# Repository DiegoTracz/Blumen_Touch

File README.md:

# Interruptor inteligente customizável
O projeto Blumen Touch, é uma solução IoT baseada no ESP8266 com o objetivo de popularizar sistemas de automação residencial de baixo custo.
<h2><b>Introdução</b></h2>
Blumen Touch é um interruptor wi-fi baseado no ESP8266 suportando até 3 botões e 3 relés de estado sólido que suportam 2A cada, 
permitindo controlar até 3 circuitos de iluminação independentes. O Blumen touch foi desenvolvido para ser instalado em caixinhas
4x2, padrão brasileiro, substituindo assim o interruptor padrão que esteja instalado. O controle pode ser feito via comando de voz, via web, smartphone ou manualmente pelos botões.
Além disso possui um interface customizável, onde é possivel colocar qualquer imagem ou foto e customizar como quiser.
<h2><b>Diagrama de fiação </b></h2>
<u1>
  <li> Ligação dos fio para os modelos B1, B2 e B3 </li>
  
  <li> Tutorial instalação:  https://youtu.be/j6668FpMcGA </li>
  <u1>
   <h2>

<h2><b>Bibliotecas necessárias</b></h2>

|  <b>Nome</b> |  <b>Link</b> |
|---|---|
| ArduinoJson  |<a href="https://github.com/bblanchon/ArduinoJson/">GIT</a>  |     
|  WebSockets | <a href="https://github.com/Links2004/arduinoWebSockets/">GIT</a>  |  
| Sirincpro  |  <a href="https://github.com/sinricpro/esp8266-esp32-sdk/">GIT</a> |   
| WifiManager  |<a href="https://github.com/tzapu/WiFiManager/">GIT</a> |   

<h2><b>Hardware</b></h2>
<u1>
  <li> Blumen Touch Placa 1, 2 e 3 teclas frente e trás</li>

  <u1>
   <h2><b>Suporte para placa</b></h2
     
 <u1>
  <li> Suporte (PLA) e espelho (acrilico) </li>

 <u1>
   <h2><b>Esquemáticos</b></h2>
     
<u1>
  <li> Esquematico frente </li>
  
  <li> Esquematico trás </li>

  <u1>
   
  <h2><b>GPIO's</b></h2>

|  <b>GPIO</b> |  <b>PINO</b> |
|---|---|
|16  | BOTÃO 1  |     
|  14 | BOTÃO 2  |  
| 12  |  BOTÃO 3|
| 05  |  RELÉ 1|   
| 04  |  RELÉ 2|   
| 02  |  RELÉ 3|   

  <h2><b>Software necessário</b></h2>
 <li><b>Sirinc Pro</b>: O Sirinc Pro é um serviço de nuvem para dispositivos inteligentes, onde de forma gratuita podemos hospedar até 3 dispositivos gratuitamente e a partir dele fazer o acionamento dos interruptores pelo aplicativo ou comando de voz.</li>
  <li> <b> Passo a passo configuração da placa utilizando a plataforma do Sinric Pro<b>: https://youtu.be/px-q5iuD3NI</li>

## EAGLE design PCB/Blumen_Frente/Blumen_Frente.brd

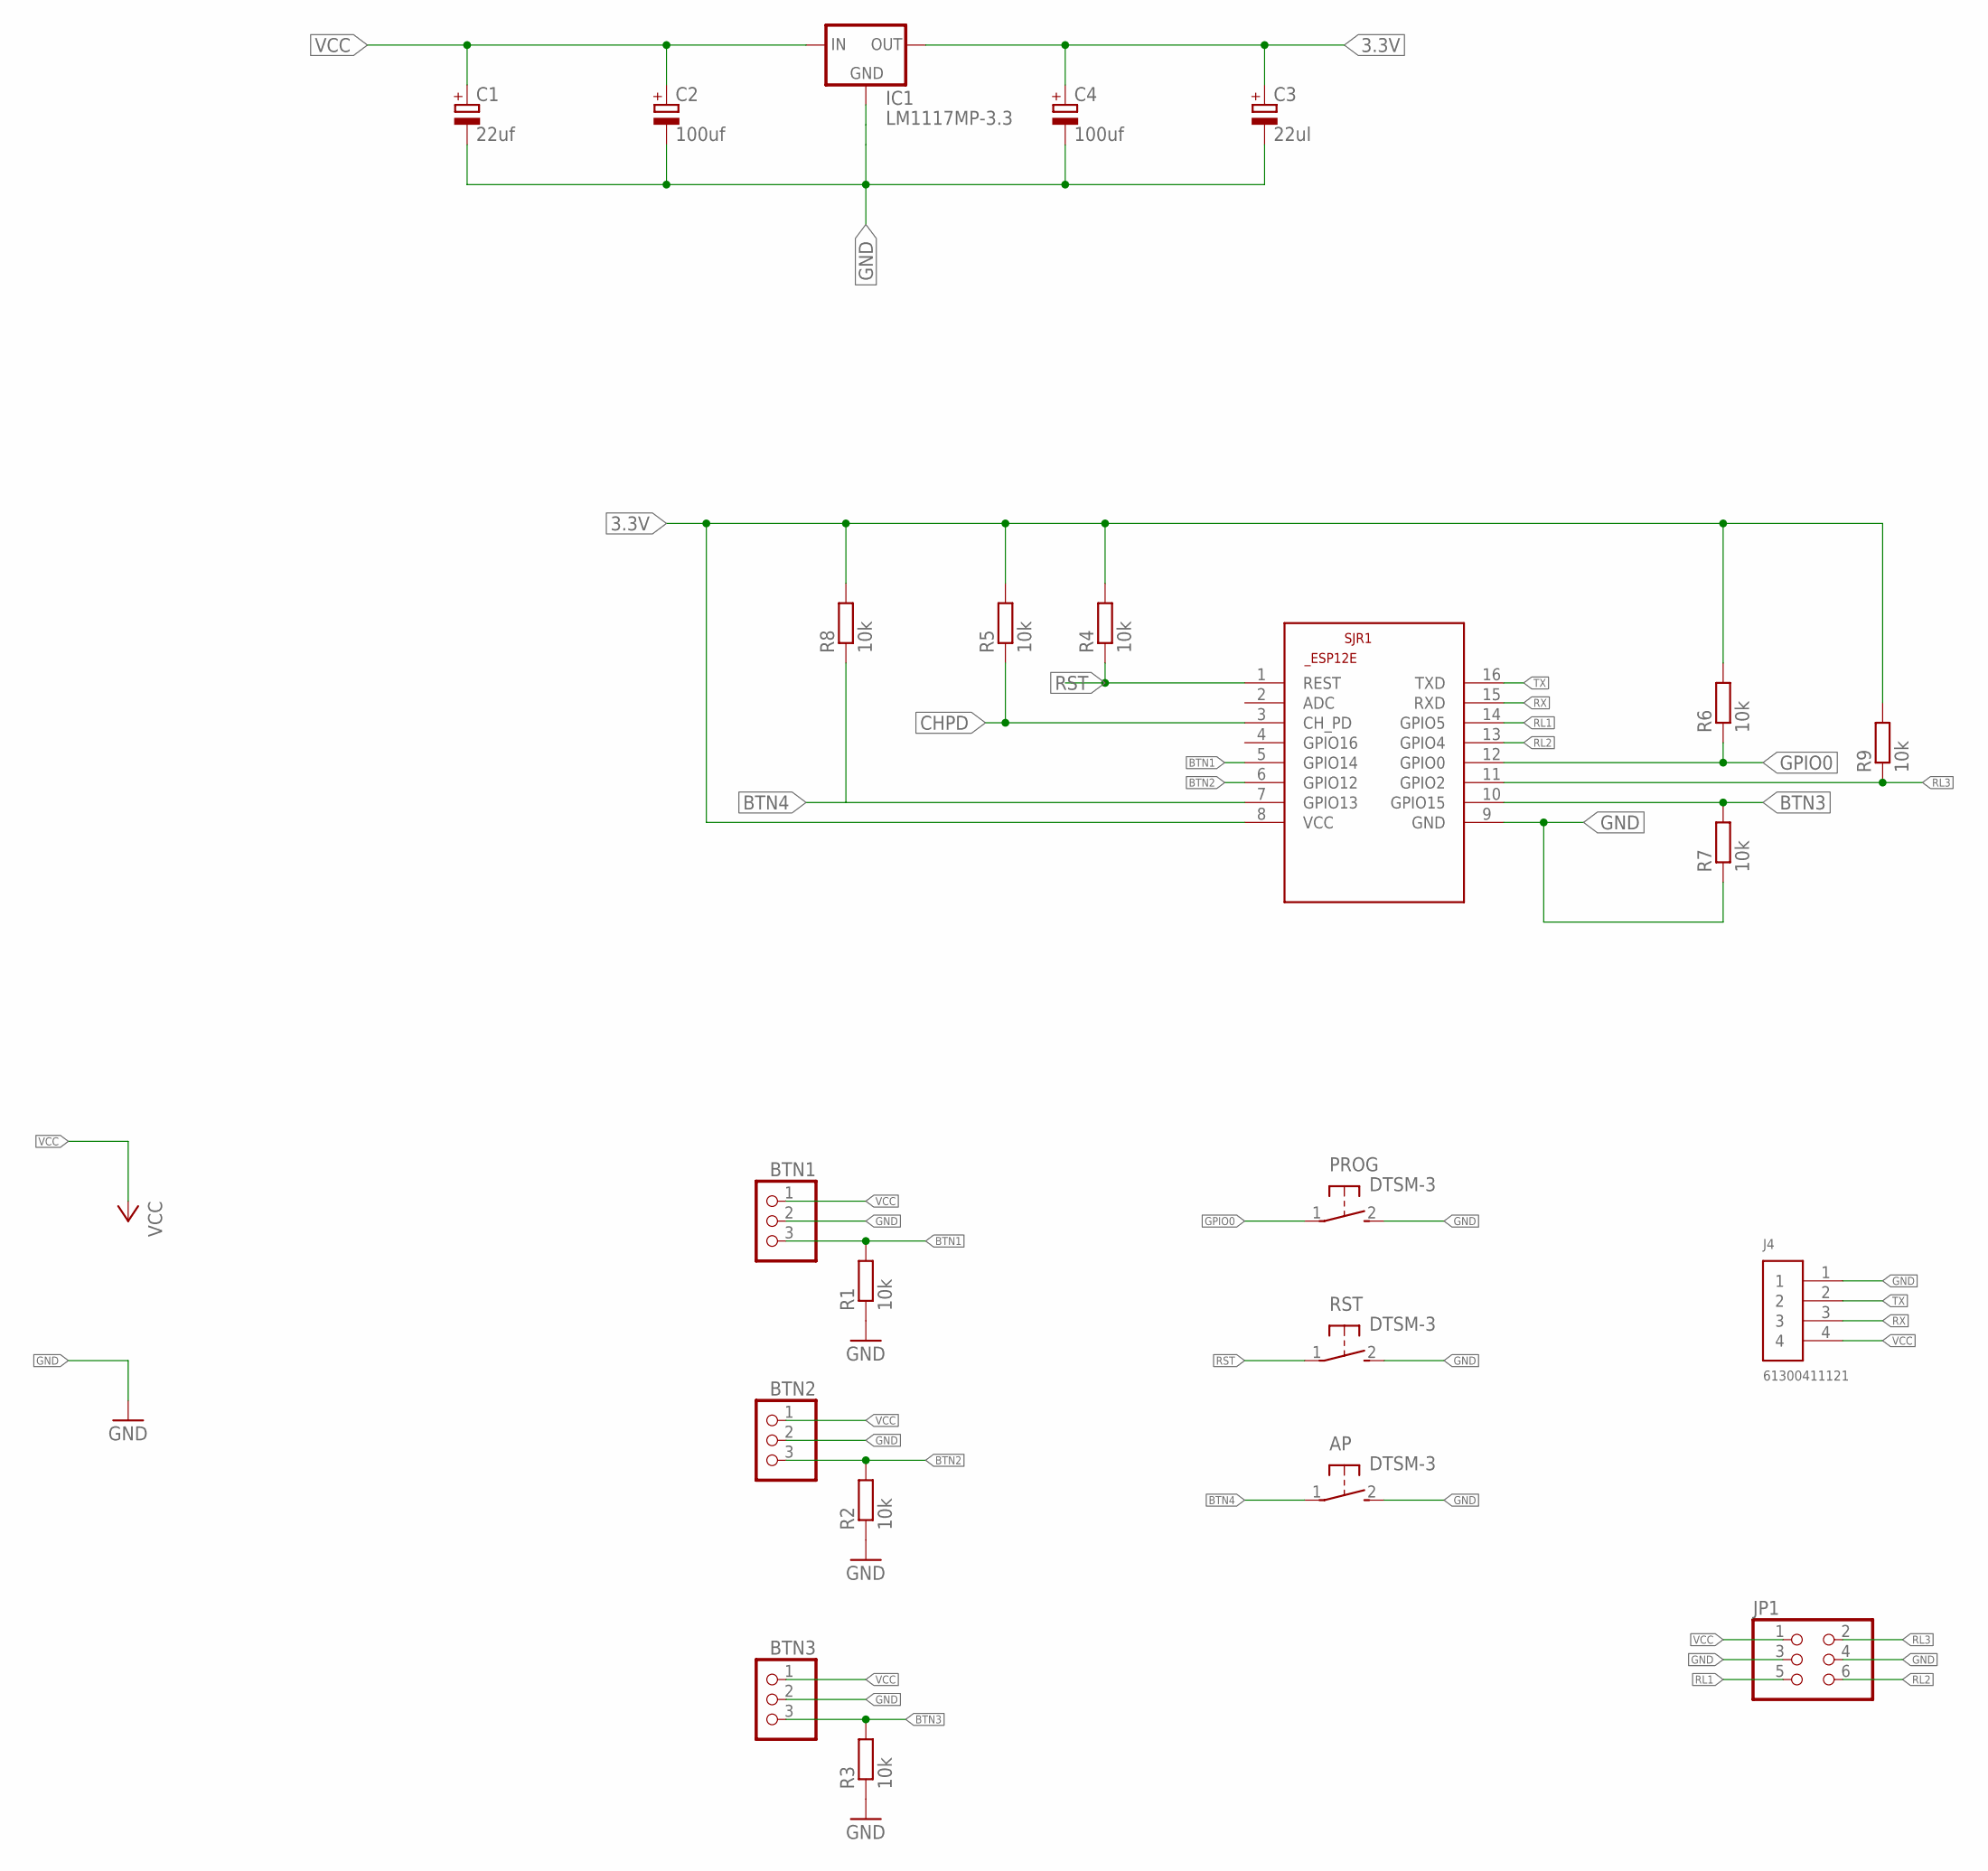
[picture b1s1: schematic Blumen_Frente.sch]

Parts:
AP: DTSM-3
BTN1, BTN2, BTN3: PINHD-1X3; 1X03
C1: 22uf; 153CLV-0505
C2, C4: 100uf; 153CLV-0605
C3: 22ul; 153CLV-0505
IC1: LM1117MP-3.3; SOT223
J4: 61300411121
JP1: PINHD-2X3; 2X03
PROG: DTSM-3
R1, R2, R3, R4, R5, R6, R7, R8, R9: 10k; R0805
RST: DTSM-3
SJR1: ESP8266-12EESP12E; ESP8266-ESP12E

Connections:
3.3V: C3.+, C4.+, IC1.2 (OUT), IC1.4 (OUT), R4.2, R5.2, R6.2, R8.2, R9.2, SJR1.8 (VCC)
BTN1: BTN1.3, R1.2, SJR1.5 (GPIO14)
BTN2: BTN2.3, R2.2, SJR1.6 (GPIO12)
BTN3: BTN3.3, R3.2, R7.2, SJR1.10 (GPIO15)
BTN4: AP.1, R8.1, SJR1.7 (GPIO13)
CHPD: R5.1, SJR1.3 (CH_PD)
GND: AP.2, BTN1.2, BTN2.2, BTN3.2, C1.-, C2.-, C3.-, C4.-, IC1.1 (GND), J4.1, JP1.3, JP1.4, PROG.2, R1.1, R2.1, R3.1, R7.1, RST.2, SJR1.9 (GND)
GPIO0: PROG.1, R6.1, SJR1.12 (GPIO0)
RL1: JP1.5, SJR1.14 (GPIO5)
RL2: JP1.6, SJR1.13 (GPIO4)
RL3: JP1.2, R9.1, SJR1.11 (GPIO2)
RST: R4.1, RST.1, SJR1.1 (REST)
RX: J4.3, SJR1.15 (RXD)
TX: J4.2, SJR1.16 (TXD)
VCC: BTN1.1, BTN2.1, BTN3.1, C1.+, C2.+, IC1.3 (IN), J4.4, JP1.1

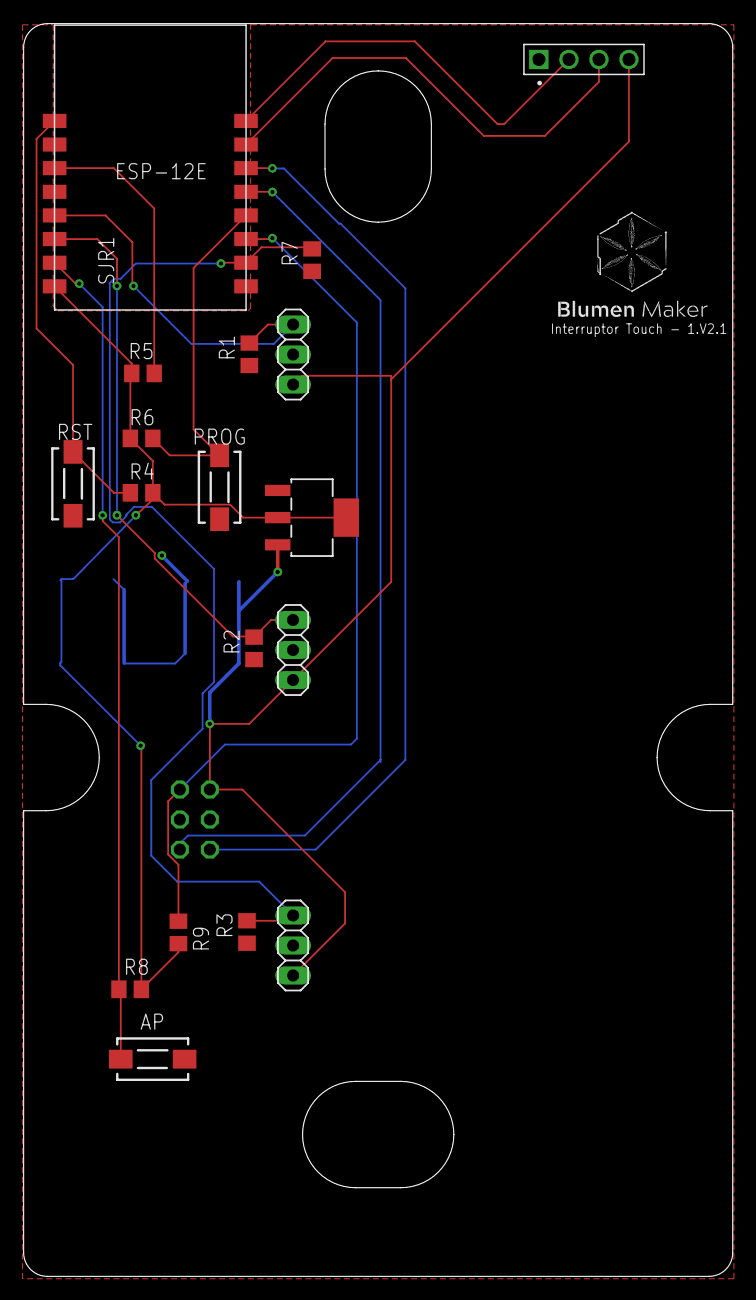
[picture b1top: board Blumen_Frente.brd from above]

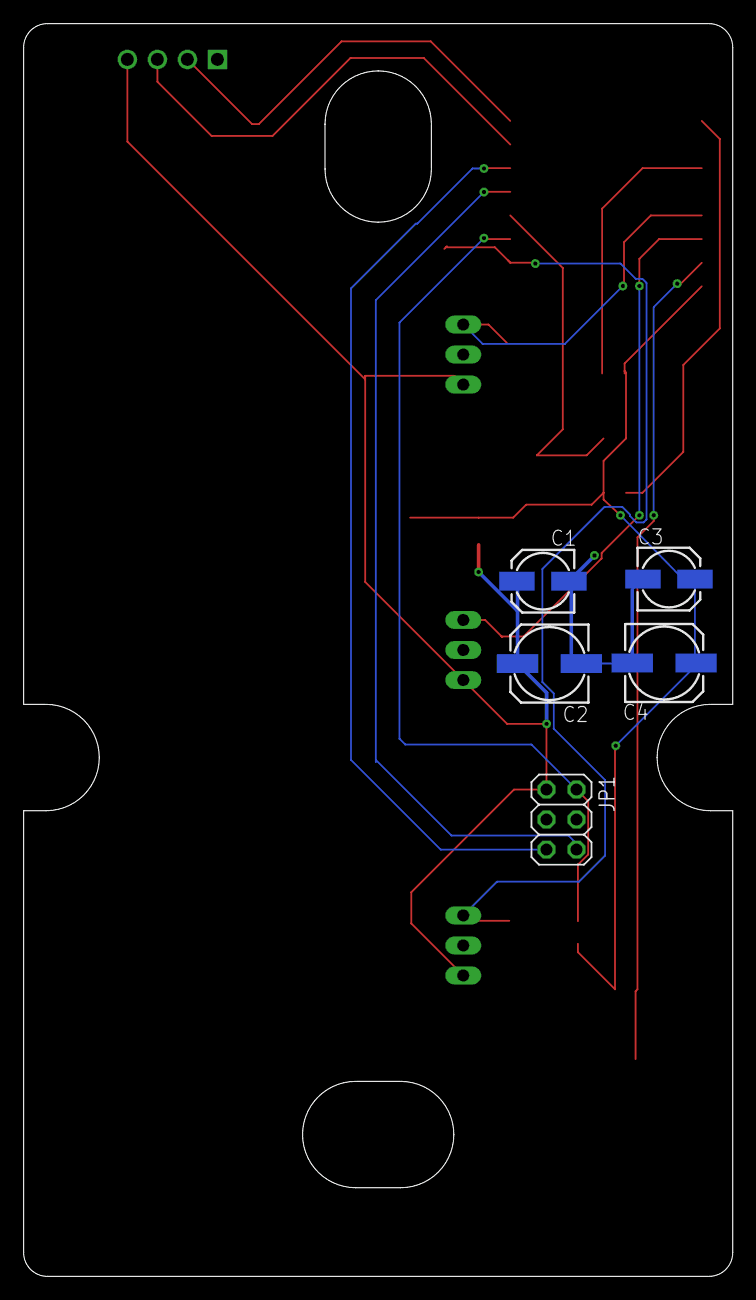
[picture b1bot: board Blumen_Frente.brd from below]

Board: 2 copper layers, 60.0 x 106.0 mm, 23 parts (5 on the bottom side), 15 nets.

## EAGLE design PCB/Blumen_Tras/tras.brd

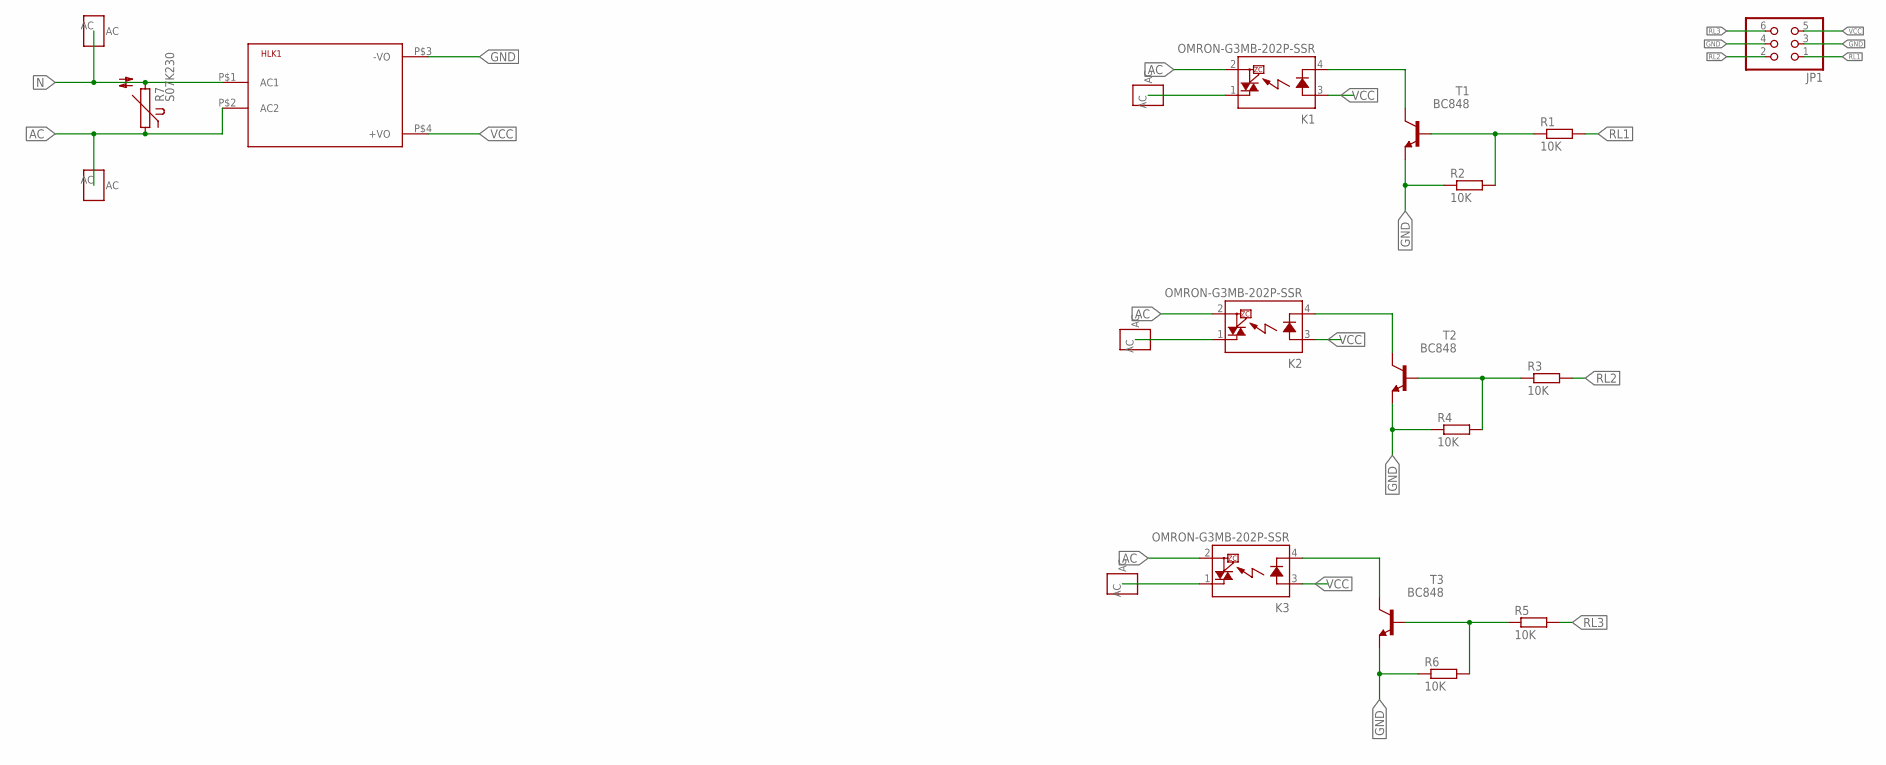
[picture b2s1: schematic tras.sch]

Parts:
AC: PAN_AC; PAD_AC
HLK1: HLK-PM013W; HLK-PM01
JP1: PINHD-2X3M; 2X03M
K1, K2, K3: OMRON-G3MB-202P-SSR
L1, L2, L3: PAN_AC; PAD_AC
N: PAN_AC; PAD_AC
R1, R2, R3, R4, R5, R6: 10K; R0805
R7: S07K230
T1, T2, T3: BC848; SOT23

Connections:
AC: AC.AC, HLK1.P$2 (AC2), K1.2 (DS2), K2.2 (DS2), K3.2 (DS2), R7.1
GND: HLK1.P$3 (-VO), JP1.3, JP1.4, R2.1, R4.1, R6.1, T1.2 (E), T2.2 (E), T3.2 (E)
L1: K1.1 (DS1), L1.AC
L2: K2.1 (DS1), L2.AC
L3: K3.1 (DS1), L3.AC
N: HLK1.P$1 (AC1), N.AC, R7.2
unnamed: K1.4 (K), T1.3 (C)
unnamed: R1.1, R2.2, T1.1 (B)
unnamed: K2.4 (K), T2.3 (C)
unnamed: R3.1, R4.2, T2.1 (B)
unnamed: K3.4 (K), T3.3 (C)
unnamed: R5.1, R6.2, T3.1 (B)
RL1: JP1.1, R1.2
RL2: JP1.2, R3.2
RL3: JP1.6, R5.2
VCC: HLK1.P$4 (+VO), JP1.5, K1.3 (A), K2.3 (A), K3.3 (A)

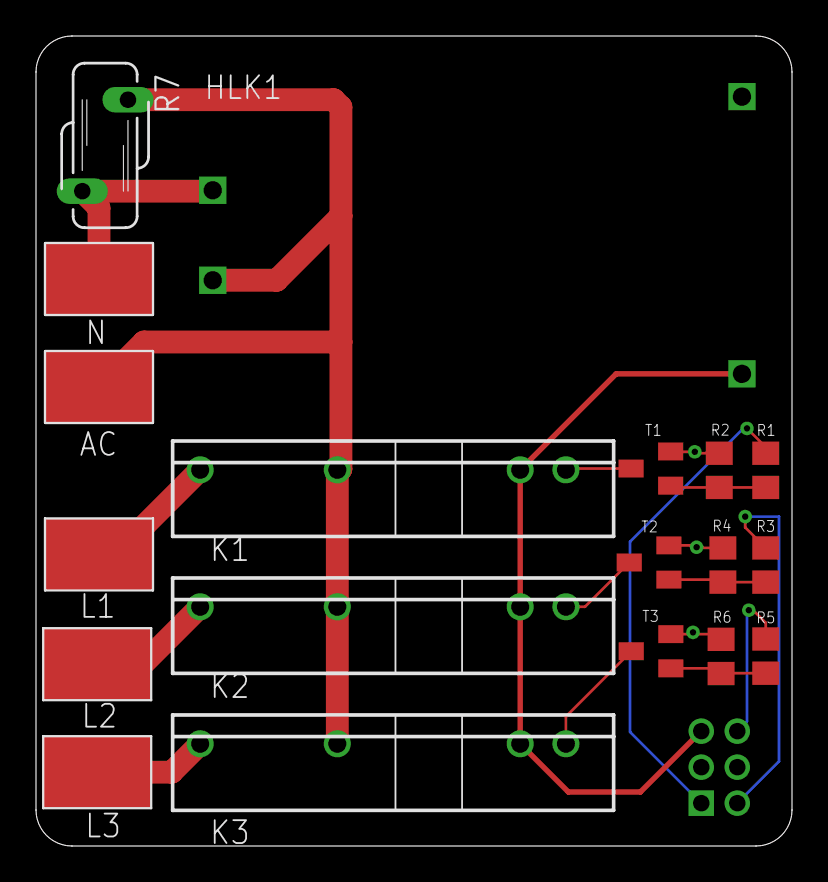
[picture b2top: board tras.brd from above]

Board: 2 copper layers, 42.0 x 45.0 mm, 20 parts (1 on the bottom side), 16 nets.

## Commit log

2021-03-30 Create PCB
2021-07-21 Create codigos
2021-08-23 Create LICENSE
